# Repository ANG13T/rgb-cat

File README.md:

# RGB Cat PCB 😺
A simple cat-shaped PCB badge to teach the basics of soldering. This PCB lets you control the color of two RGB lights using three potentiometers.

*Article coming soon!*

## Materials
- 6x 100ohm Resistors
- 2x RGB LEDs with Common Cathode (LED_RKGB)
- 3x Trim Potentiometers
- 3V Coin Cell Battery 
- 3V 1060 Battery Cell Holder
- SPDT Slide Switch

## Schematic

## PCB Design

## Preview

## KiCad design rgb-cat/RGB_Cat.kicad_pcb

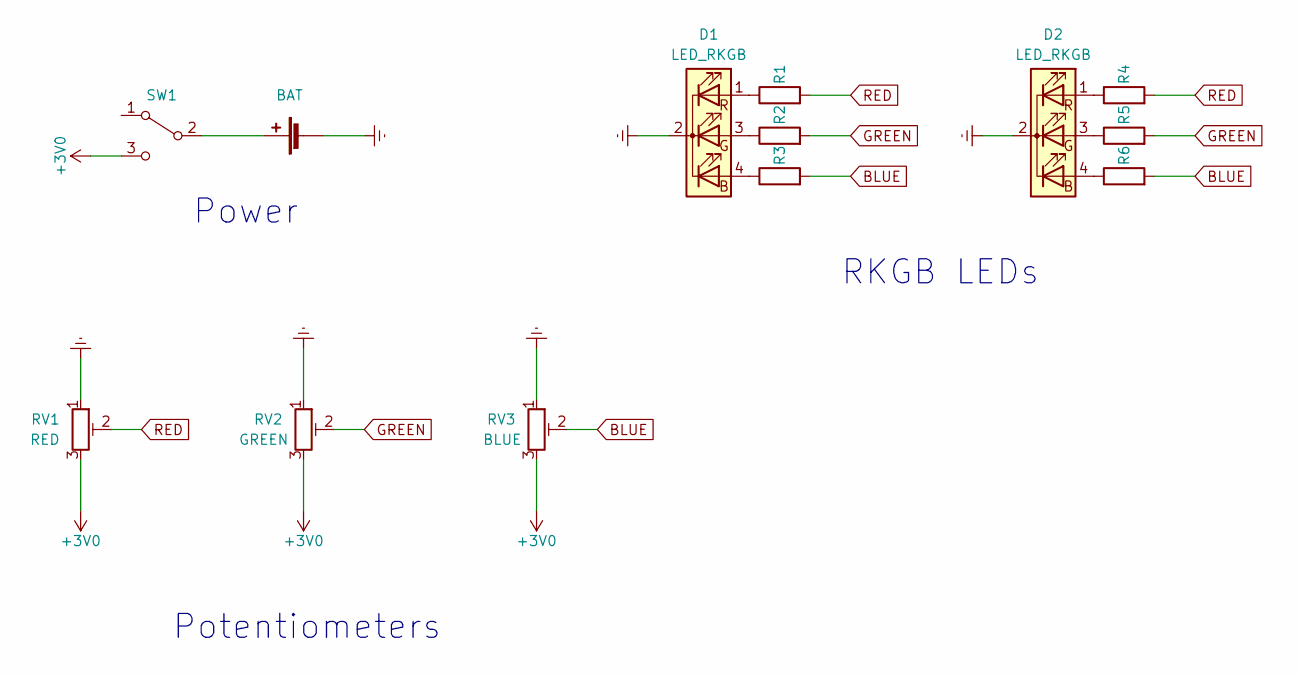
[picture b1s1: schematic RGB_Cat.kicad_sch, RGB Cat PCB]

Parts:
BT1: BAT; BatteryHolder_Keystone_107_1x23mm
D1, D2: LED_RKGB; LED_D5.0mm-4_RGB_Wide_Pins
R1, R2, R3, R4, R5, R6: R; R_Axial_DIN0309_L9.0mm_D3.2mm_P20.32mm_Horizontal
RV1: RED; Potentiometer_Bourns_3386P_Vertical
RV2: GREEN; Potentiometer_Bourns_3386P_Vertical
RV3: BLUE; Potentiometer_Bourns_3386P_Vertical
SW1: SW_SPDT; Schiebeschalter SS-12D00.kicad_mod

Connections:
+3V0: RV1.3, RV2.3, RV3.3, SW1.3 (C)
BLUE: R3.2, R6.2, RV3.2
GNDREF: BT1.2 (-), D1.2 (K), D2.2 (K), RV1.1, RV2.1, RV3.1
GREEN: R2.2, R5.2, RV2.2
unnamed: BT1.1 (+), SW1.2 (B)
unnamed: D1.4 (BA), R3.1
unnamed: D1.3 (GA), R2.1
unnamed: D1.1 (RA), R1.1
unnamed: D2.4 (BA), R6.1
unnamed: D2.3 (GA), R5.1
unnamed: D2.1 (RA), R4.1
RED: R1.2, R4.2, RV1.2

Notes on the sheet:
Power
RKGB LEDs
Potentiometers

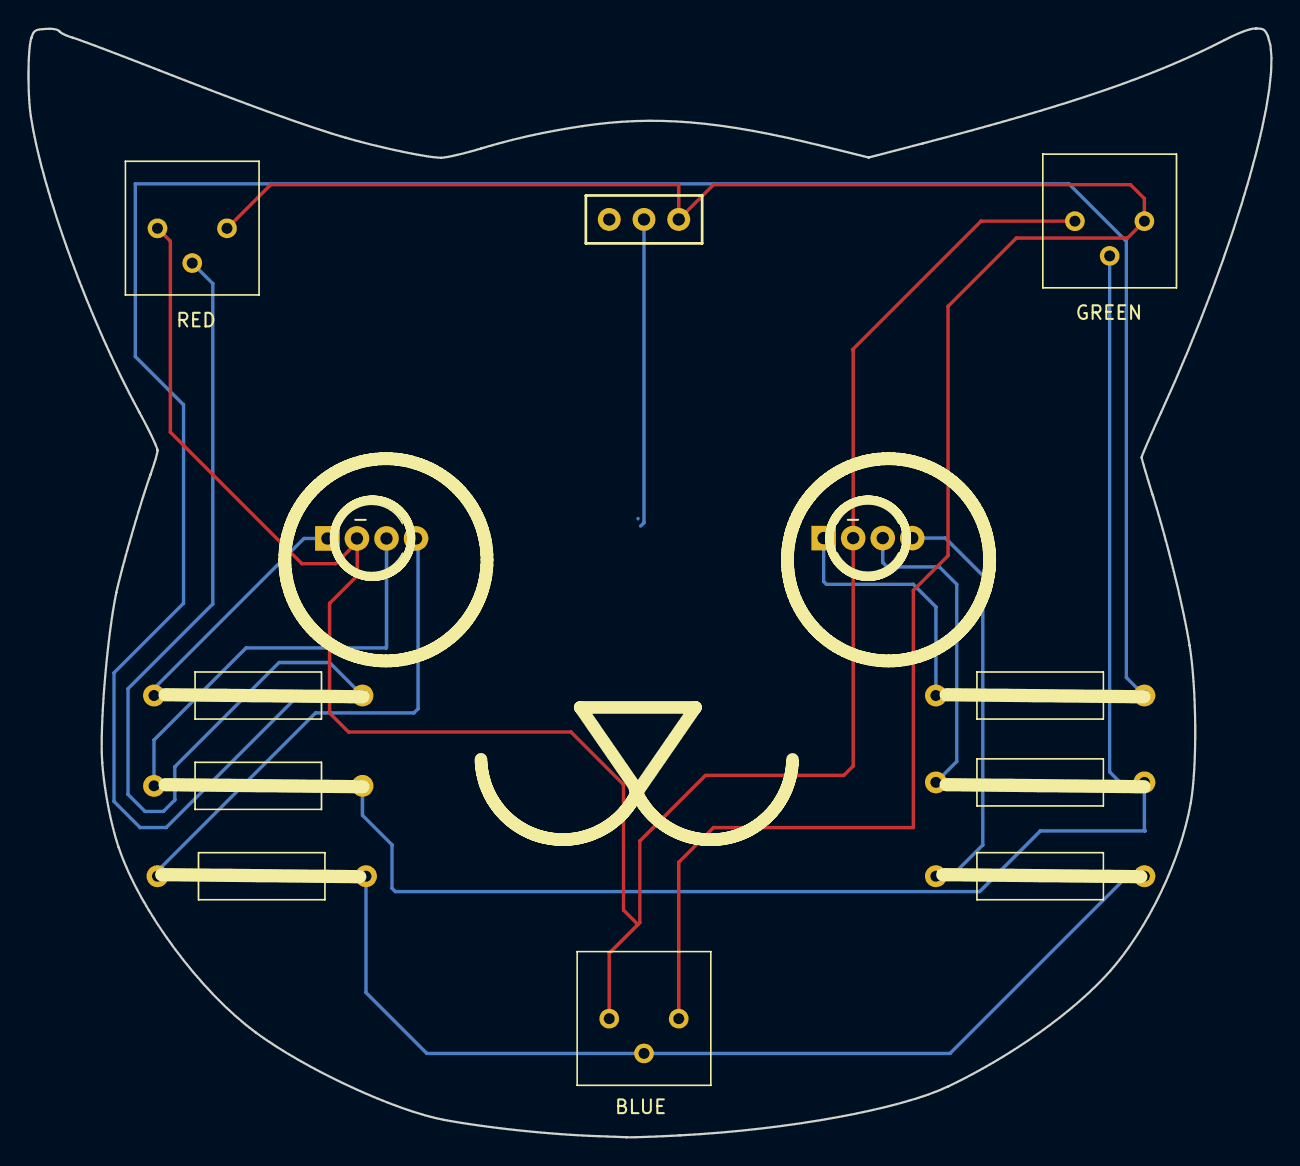
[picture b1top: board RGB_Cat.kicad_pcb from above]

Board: 2 copper layers, 90.9 x 81.0 mm, 13 parts (1 on the bottom side), 12 nets.

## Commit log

2023-04-08 init commit
2023-04-08 feat: init kicad files
2023-04-08 feat: init assets
2023-04-08 Create LICENSE
